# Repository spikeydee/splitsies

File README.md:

# splitsies

splitsies is a 34-key ortholinear split keyboard with a multi-layered combo-switching keymap. Inspired by @pierrechevalier83's [ferris](https://github.com/pierrechevalier83/ferris), @makenova's [micro-redox-split](https://github.com/makenova/micro_redox/tree/main/micro_redox_split), and @manna-harbor's [miryoku layout](https://github.com/manna-harbour/miryoku/). 

Built around an ortholinear, homerow-centric typing layout, and personally the use of the Workman layout, my splitsies keyboard hopes to achieve a typing workflow with minimum diagonal and horizontal movements of the fingers (minimal finger travel) that hopefully will become more intuitive over time. 

## Overall Features
- THT/soldered only with choc spacing.
- Diodeless
- Reversible PCB & MCU
- I also designed a one-piece, press-fit case that covers the PM (although the PM cover still needs tweaking).

## Required Parts
- 2x Pro Micro microcontroller / anything else with the same footprint
  - It is possible to use a nice!nano as well to make it wireless and rechargeable
- 2x TRRS jacks
- 1x TRRS cable
- 2x Reset switch (optional)

## Layout

Using mostly @manna-harbor's [miryoku layout](https://github.com/manna-harbour/miryoku/), the biggest changes I've made are making the third layer on each side accessible on a 2-key only thumb row through the use of QMK's combos. Where pressing the thumb row keys individually would get you to the first and second layout, pressing both keys at the same time would get you to the tertiary layer of the keymap on the other side of the splitsies keyboard. Minor changes I've made are to the placement of the arrow keys becoming more WASD-like due to preference, a few tweaks to a few more mouse/page navigation buttons (scrolling, page up/down, etc.), and as well as a few key placements the media layer.

## Firmware
- You can find the firmware for the splitsies in my QMK fork dev branch [here](https://github.com/spikeydee/qmk_firmware/tree/spikeydee_dev/keyboards/splitsies/).
- You can also see the my modified miryoku keyboard layout in my userspace [here](https://github.com/spikeydee/qmk_firmware/tree/spikeydee_dev/users/spikeydee).

## Version Differences
I tried my best to prototype each version, following @ruiqimao's [keyboard pcb making guide](https://github.com/ruiqimao/keyboard-pcb-guide). So luckily for most of my iterations, I did not have to rework the traces and footprints at all on KiCad after my first go with ordering them to be made through JLCPCB back then. I'll note albeit the few tweaks I made on each version.

V1 and V2's PCB and case design are good to go (V2 is slightly more compact–therefore is my preferred version) whereas V3 still needs a bit more testing (I'll explain further down below). The 3D printed slip-on case .stl fits both the V1 and V2. 

N.B.: I lost my slide-in case .stl files with the overhanging attached pro micro cover as well as the original with the separated pro micro cover so I need to approximately remake those files in the future.

# V1

I've used split keyboards with thumb buttons a handful of times before (e.g.: microdox, minidox, ferris) but even slightly before using those keyboards, I've been a fan of having an ortholinear layout so I decided I wanted to combine them both. Wanting symmetry, simplicity, and compactness in the design, I opted to make the design reversible, diodeless, and to achieve the smallest footprint possible, I mounted the trrs jack below the third column (and in testing surprisingly does not interfere with typing at all as long as the trrs cable head isn't bulky).

I designed the case to be a slide then press-fit case which has an over-hanging cover for the pro micro where you can take off the supports after printing. I designed the height of the case to be as tall as the keyswitch + keycap's low point when they are pressed down. If the case is still a bit loose then I usually fix that with a bit of hot glue (the image is actually from the version without the attached overhanging PM cover though).

The V1 to me is more of a proof of concept that maybe I could bring all these concepts together into one coherent keyboard, and when I did, if I could get used to the layout and form-factor itself. To me it was a great success in proving all that as since 2021, I've exclusively used the splitsies as my main keyboard and have remembered and gotten used to it's layout & layers after the first few months of using it (although I was already used to the miryoku layout because I used it on other split keyboards before as well). Touch-typing was a non-issue as well because I didn't even have legends on my keycaps since lettered choc keycaps were expensive back then. 

Having a diodeless keyboard made it so that NKRO was a non-issue as well during gaming. I reverted to a toggleable basic WASD layout with the modifier keys on the left since having to re-map everything and also having the modifier keys on the homerow was inconvenient and made most games be practically unplayable.

# V2

The V2 was a much simpler iteration as I gave myself wiggle room of a few milimeters on the footprint of the PCB on the V1, so I just made everything a bit tighter on the V2. I moved the placement slightly on of the MCU and recessed TRRS jacks a bit more as well. The case design didn't really change because the gaps for the microusb port and TRRS jack still aligns with no fitment issues. Visually, the changes aren't that discernable but It gave me a bit more peace of mind that I could make the board footprint more compact.

# V3

For the V3, I wanted to try making a wireless bluetooth version of the splitsies. Back then my budget was tight but time was plentiful, so I opted on trying to use the Seeeduino XIAO BLE microcontroller/ESP32C3 (which also just came out back then in 2022). Wanting to always make the PCB footprint even smaller + out of curiosity and inspiration from @tominabox1's [BLe Chiffre](https://geekhack.org/index.php?topic=111207.0), I decided that I wanted to power the keyboard using a rechargeable coin cell battery as well. Due to the fewer amounts of pins on the microcontroller, I had to go back to using diodes for a row-to-column keyboard matrix setup as I don't think I can handle a keyboard being smaller than 34 keys haha.

As you can see I was able to get the prototype made, but with some glaring issues: 
- I was in Indonesia at the time and wasn't able to order the PCB through JLCPCB like I usually do, so I looked around for local small manufacturers, which I found, but most of them required me to either convert the kicad files to eagle or if I recall correctly they were able to work directly with the .gerber files. I had the readjust the size of the traces and the gaps between them as well due to their machines being unable to print that closely. All was going well but unlike the online printing companies where they know that when there's silkscreen on top of certain pads or components, the local place just straight up put the silkscreen on ALL THE PADS ON THE PCB?!! So I had to scratch a lot of it off to get even a bit of solder to stick to the pads, and by the time I finished soldering the MCU and all the diodes (I had to jump a few traces too since I decimated some in the process of silkscreen scratching), I was able to barely program ZMK to work with the keyboard and was too frustrated to even keep going...

I didn't get to updating the case yet for this design because I wasn't able to follow through with finishing the keyboard yet as mentioned above. I uploaded the KiCad files for the original V3 and not the one adjusted for the indonesian place's parameters.

## Additional Remarks + Future Plans

While we're on the subject of wireless: Later on I tried again but on the V2 using a nice!nano, but I wasn't able to get it working using ZMK, since at that time they didn't have that much documentation for custom diodeless keyboard support + I wasn't technically savvy enough to figure it out on my own :\ + wiring and soldering batteries scared the heck out of me too back then HAHA.

I'm hoping I could get the V2 with the nice!nano and the V3 working some time in the future, remaking my 3d printed old case design,and designing + printing a nice machined metal/aluminum case for it too so that I can have a portable, rechargeable, and robust custom keyboard that suits my preferences exactly.

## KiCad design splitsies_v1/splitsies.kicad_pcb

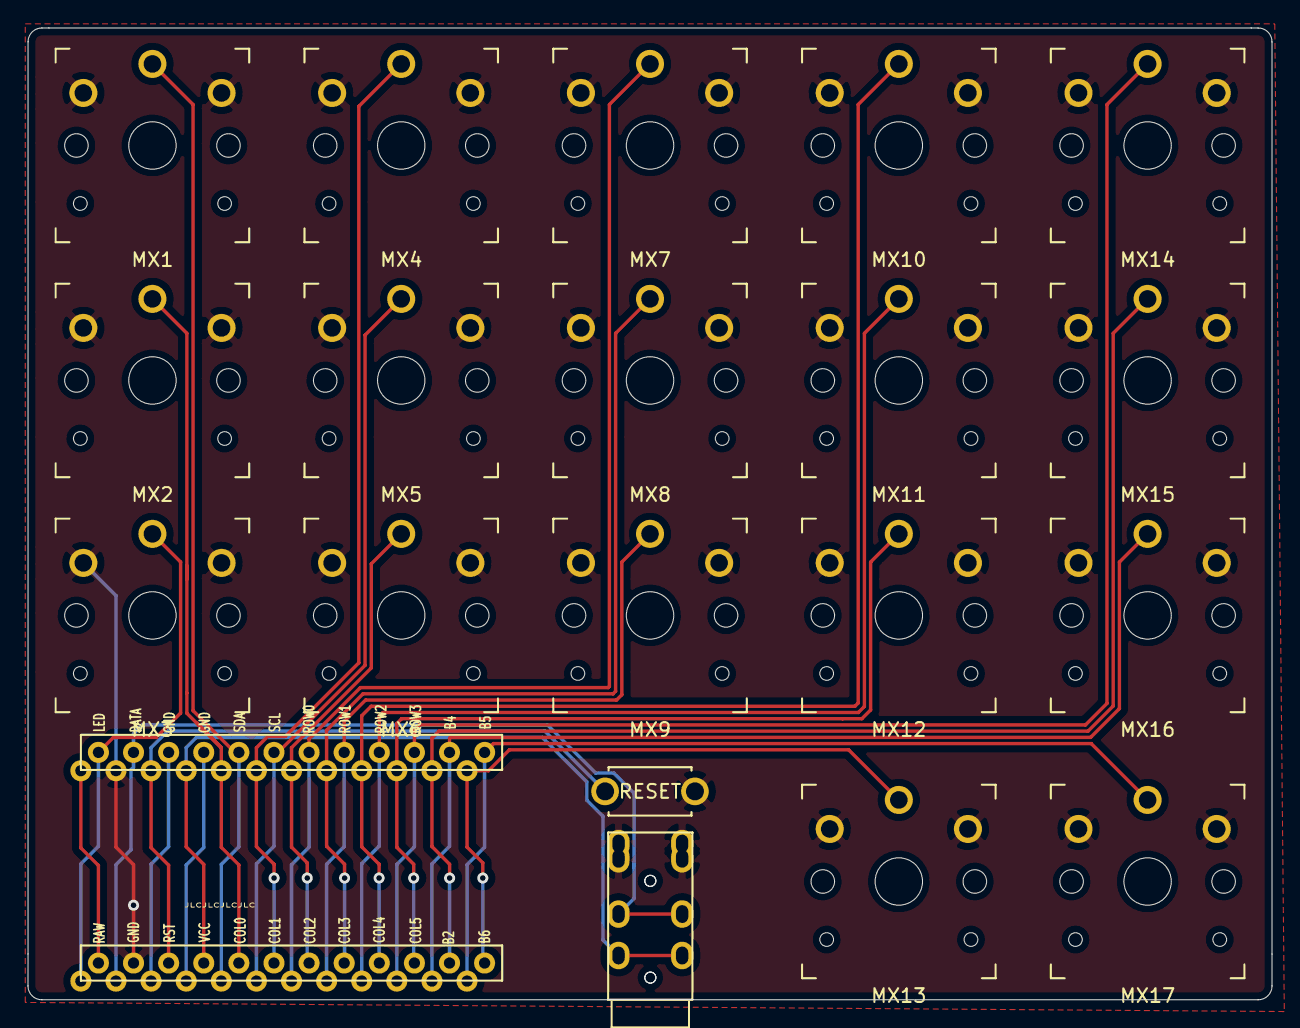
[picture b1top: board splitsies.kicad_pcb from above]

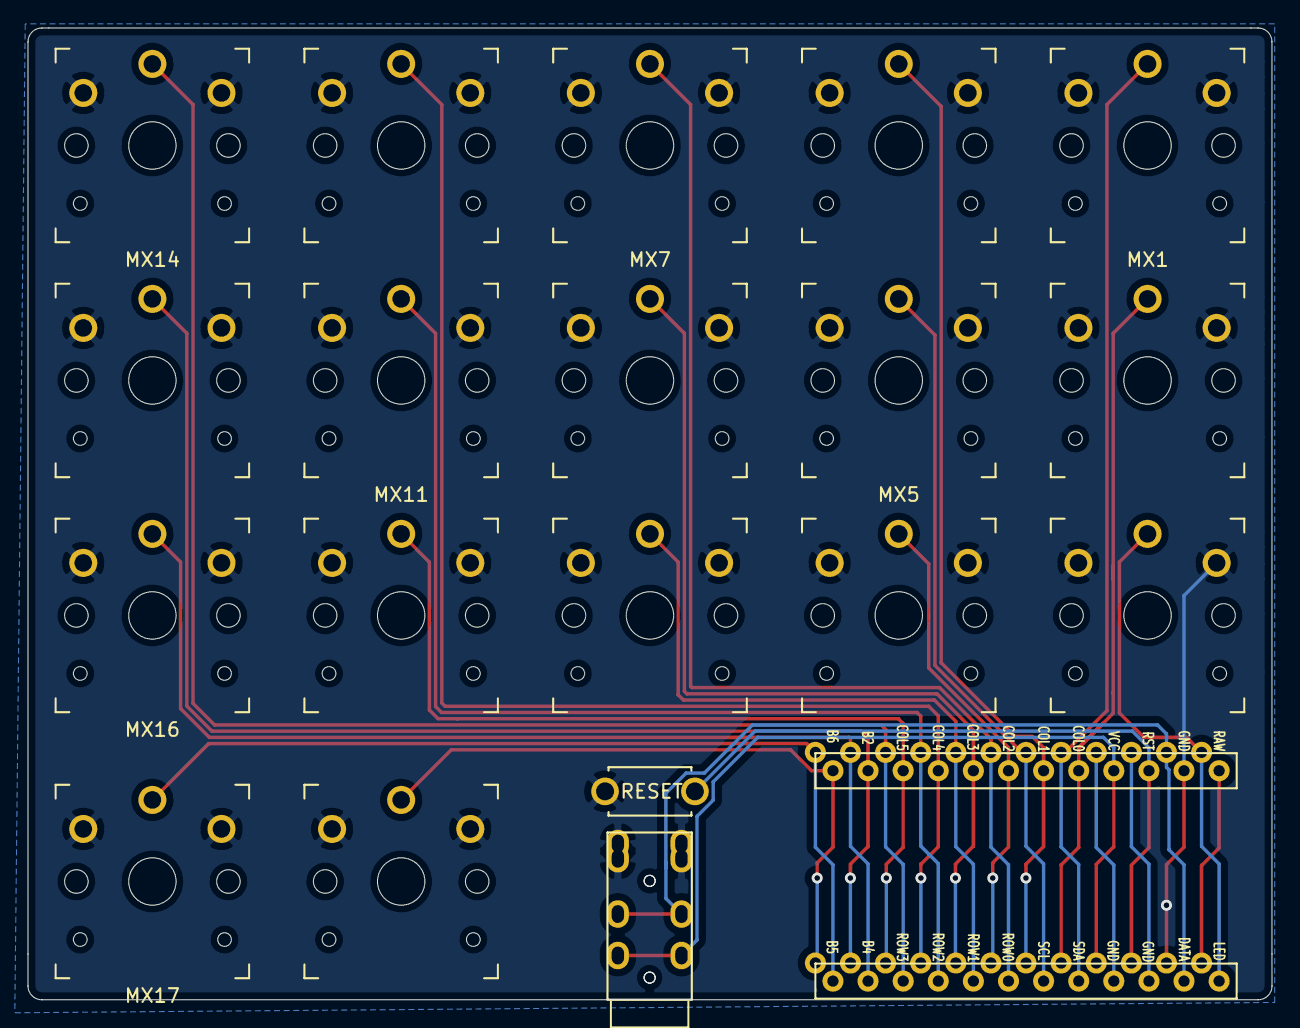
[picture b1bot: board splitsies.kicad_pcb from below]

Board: 2 copper layers, 90.0 x 70.3 mm, 21 parts (2 on the bottom side), 21 nets.

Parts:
MX1, MX2, MX3, MX4, MX5, MX6, MX7, MX8, MX9, MX10, MX11, MX12, MX13, MX14, MX15, MX16, MX17: MX-NoLED; SW_PG1350_reversible
SW1: SW_SPST; ResetSW
U1: ProMicro; ProMicro_v2
U2, U3: TRRS; TRRS-PJ-320A-no-Fmask

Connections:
+5V: U1.21, U2.4, U3.4
DATA0: U1.2, U2.3, U3.3
GND: MX1.2, MX2.2, MX3.2, MX4.2, MX5.2, MX6.2, MX7.2, MX8.2, MX9.2, MX10.2, MX11.2, MX12.2, MX13.2, MX14.2, MX15.2, MX16.2, MX17.2, SW1.2, U1.23, U2.1, U2.2, U3.1, U3.2
unnamed: SW1.1, U1.22
S1: MX1.1, U1.5
S2: MX2.1, U1.20
S3: MX3.1, U1.1
S4: MX4.1, U1.19
S5: MX5.1, U1.6
S6: MX6.1, U1.18
S7: MX7.1, U1.7
S8: MX8.1, U1.17
S9: MX9.1, U1.8
S10: MX10.1, U1.16
S11: MX11.1, U1.9
S12: MX12.1, U1.15
S13: MX13.1, U1.13
S14: MX14.1, U1.10
S15: MX15.1, U1.14
S16: MX16.1, U1.11
S17: MX17.1, U1.12

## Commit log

2025-10-14 Update README.md
    added basic description to the splitsies project, will add pictures and each rev description next.
2025-10-14 Update README.md
    formatting
2025-10-14 updated description fully, need to add images next!
2025-10-14 updated intro a bit (STILL NEED PICS)
2025-10-16 description (still need to add the pics)
2025-10-16 description (add images)
2025-10-16 more desc. (still need pics)
2025-10-16 description, adding files and pics now
2025-10-16 added all kicad files, stl, and images.
2025-10-16 finally added pictures!!!
2025-10-16 fixed picture links, more desc.
2025-10-16 missed a few things
2025-10-16 cleaned up unecessary kicad files.
2025-10-23 typo
